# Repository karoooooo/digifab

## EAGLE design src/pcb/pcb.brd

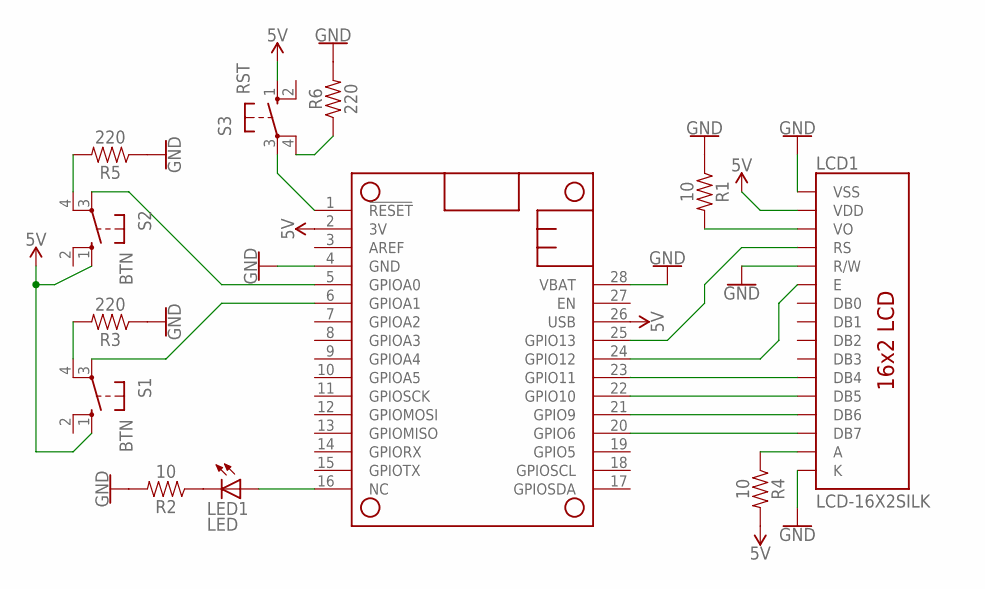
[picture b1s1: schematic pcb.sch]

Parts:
LCD1: LCD-16X2SILK; LCD-16X2
LED1: LED; LED5MM
MS2: FEATHERWING
R1, R2, R4: 10; AXIAL-0.3
R3, R5, R6: 220; 0603
S1, S2: BTN; B3F-40XX-ROUND
S3: RST; B3F-40XX-ROUND

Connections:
5V: LCD1.2 (VDD), MS2.2 (3V), MS2.26 (USB), R4.P$2 (2), S1.1 (S), S2.1 (S), S3.1 (S)
GND: LCD1.1 (VSS), LCD1.5 (R/W), LCD1.16 (K), MS2.4 (GND), MS2.28 (VBAT), R1.P$1 (1), R2.P$2 (2), R3.1, R5.1, R6.2
unnamed: R3.2, S1.4 (P1)
unnamed: R5.2, S2.4 (P1)
unnamed: MS2.3 (AREF), S1.2 (S1)
unnamed: LCD1.14 (DB7), MS2.20 (GPIO6)
unnamed: LCD1.13 (DB6), MS2.21 (GPIO9)
unnamed: LCD1.12 (DB5), MS2.22 (GPIO10)
unnamed: LCD1.11 (DB4), MS2.23 (GPIO11)
unnamed: MS2.6 (GPIOA1), S1.3
unnamed: LED1.A, MS2.16 (NC)
unnamed: LED1.K (C), R2.P$1 (1)
unnamed: LCD1.15 (A), R4.P$1 (1)
unnamed: MS2.1 (!RESET), S3.3
unnamed: LCD1.3 (VO), R1.P$2 (2)
unnamed: LCD1.4 (RS), MS2.25 (GPIO13)
unnamed: R6.1, S3.4 (P1)
unnamed: MS2.5 (GPIOA0), S2.3
unnamed: LCD1.6 (E), MS2.24 (GPIO12)

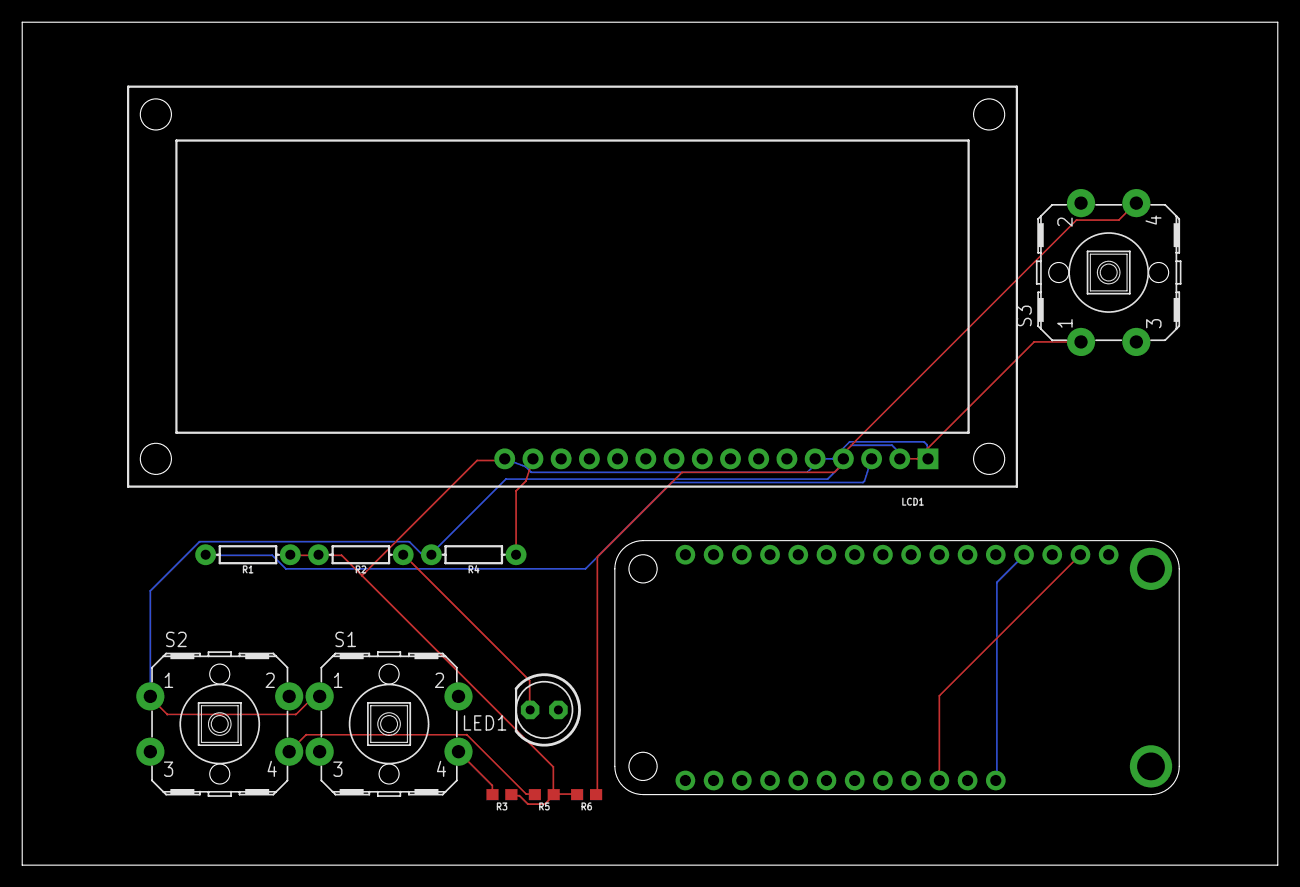
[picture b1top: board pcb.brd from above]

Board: 2 copper layers, 113.0 x 75.9 mm, 12 parts (0 on the bottom side), 19 nets.

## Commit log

2022-09-05 added folder with basic files
2022-09-19 added basic html
2022-09-19 moved files out a level
2022-09-19 basic styling and responsivity added
2022-09-19 adding right link for stylesheet?
2022-09-19 is this the way?
2022-09-19 link?
2022-09-19 link as usual?
2022-09-19 this must be right..
2022-09-19 add right link
2022-09-19 added link
2022-09-19 working link..
2022-09-19 links changed
2022-09-19 connected to CSS, not sassy, and progressed with design
2022-10-01 added js and implemented more features
2022-10-01 cleaned up css
2022-10-01 adjusting layout responsi[ve/b]y
2022-10-01 more css..
2022-10-01 away with js
2022-10-01 small update css
2022-10-02 last changes for now
2022-10-02 substance and responsivity
2022-10-02 style
2022-10-02 clean up
2022-10-02 css..
2022-10-02 fixing random things
2022-10-02 cleaning up
2022-10-02 added second page and updated links
2022-10-05 added a new font and played around with header flex
2022-10-05 more adjustment to css
2022-10-05 footer buttons
2022-10-05 css adjustments
2022-10-31 link visibility on hover/active
2022-11-01 adjusted sizes and layout, added new reading font
2022-11-27 added some images and adjusted layout for more assignments
2022-11-27 uploaded the css...
2022-11-27 changed nav to start off as display='none'
2022-11-27 quite finished
2022-11-27 added link to .3mf-file
2022-11-27 språkforbedring
2022-11-27 minor css change
2022-11-27 a change
2022-11-27 some final changes
2022-11-27 fiinal
2022-11-27 name change of an img
2022-11-28 embarrasingly wrong number
2023-01-21 awaited updates
2023-02-26 minimumskrav?
2023-02-26 added link to github
2023-02-26 added imgs
2023-02-26 questionmark
2023-03-26 first draft pcb
2023-03-26 more changes
2023-03-26 last
2023-03-26 small change
2023-04-21 css bug fix
2023-05-28 sluttprosjekt
2023-05-30 more
2023-05-30 almost done
2023-05-30 okiiii
2023-05-30 good night

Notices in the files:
parts and their libraries:
SparkFun-Displays: Licensing: Creative Commons ShareAlike 4.0 International - https://creativecommons.org/licenses/by-sa/4.0
